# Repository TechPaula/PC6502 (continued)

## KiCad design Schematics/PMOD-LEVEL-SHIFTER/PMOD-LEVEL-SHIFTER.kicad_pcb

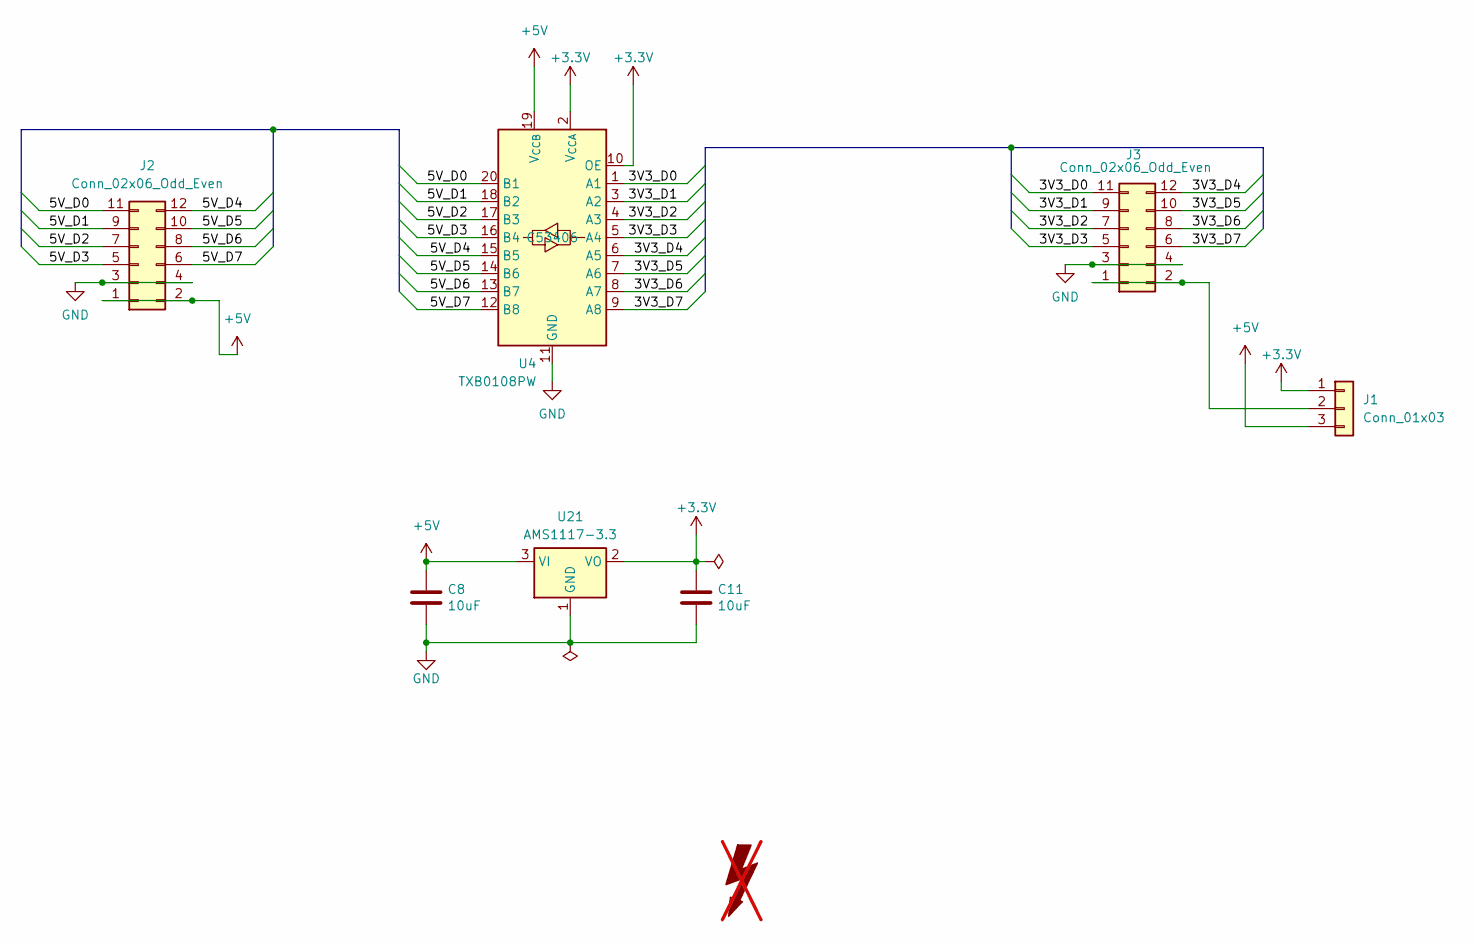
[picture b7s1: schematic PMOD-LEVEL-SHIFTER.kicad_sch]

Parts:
C8, C11: 10uF; C_0805_2012Metric; ManufacturerPN C3216X7R1E475M085AB; LCSC C15850
FOX1: SYM_Flash_Large; Fox_avatar_18mm; LCSC DNF; not fitted
J1: Conn_01x03; PinHeader_1x03_P2.54mm_Vertical
J2: Conn_02x06_Odd_Even; PinHeader_2x06_P2.54mm_Horizontal
J3: Conn_02x06_Odd_Even; PinSocket_2x06_P2.54mm_Horizontal
U4: TXB0108PW; TSSOP-20_4.4x6.5mm_P0.65mm; LCSC C53406
U21: AMS1117-3.3; SOT-223-3_TabPin2; LCSC C6186

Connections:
+3.3V: C11.1, J1.1, U4.2 (V_{CCA}), U4.10 (OE), U21.2 (VO)
+5V: C8.1, J1.3, J2.1, J2.2, U4.19 (V_{CCB}), U21.3 (VI)
/3V3_D0: J3.11, U4.1 (A1)
/3V3_D1: J3.9, U4.3 (A2)
/3V3_D2: J3.7, U4.4 (A3)
/3V3_D3: J3.5, U4.5 (A4)
/3V3_D4: J3.12, U4.6 (A5)
/3V3_D5: J3.10, U4.7 (A6)
/3V3_D6: J3.8, U4.8 (A7)
/3V3_D7: J3.6, U4.9 (A8)
/5V_D0: J2.11, U4.20 (B1)
/5V_D1: J2.9, U4.18 (B2)
/5V_D2: J2.7, U4.17 (B3)
/5V_D3: J2.5, U4.16 (B4)
/5V_D4: J2.12, U4.15 (B5)
/5V_D5: J2.10, U4.14 (B6)
/5V_D6: J2.8, U4.13 (B7)
/5V_D7: J2.6, U4.12 (B8)
GND: C8.2, C11.2, J2.3, J2.4, J3.3, J3.4, U4.11 (GND), U21.1 (GND)
unnamed: J1.2, J3.1, J3.2

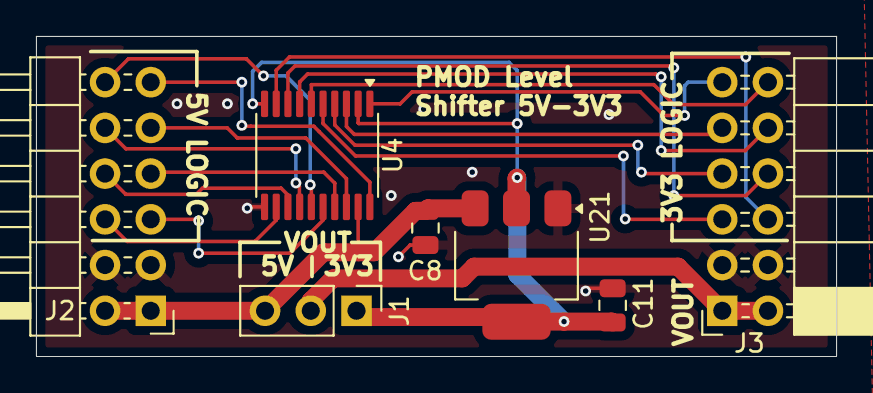
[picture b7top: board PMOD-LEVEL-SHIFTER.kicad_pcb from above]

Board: 4 copper layers, 44.5 x 17.8 mm, 8 parts (1 on the bottom side), 20 nets.

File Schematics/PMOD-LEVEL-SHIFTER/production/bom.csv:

Designator,Footprint,Quantity,Value,LCSC Part #
"C11, C8",0805,2,10uF,C15850
FOX1,Fox_avatar_18mm,1,SYM_Flash_Large,DNF
J1,PinHeader_1x03_P2.54mm_Vertical,1,Conn_01x03,
J2,PinHeader_2x06_P2.54mm_Horizontal,1,Conn_02x06_Odd_Even,
J3,PinSocket_2x06_P2.54mm_Horizontal,1,Conn_02x06_Odd_Even,
U21,SOT-223-3_TabPin2,1,AMS1117-3.3,C6186
U4,TSSOP-20_4.4x6.5mm_P0.65mm,1,TXB0108PW,C53406

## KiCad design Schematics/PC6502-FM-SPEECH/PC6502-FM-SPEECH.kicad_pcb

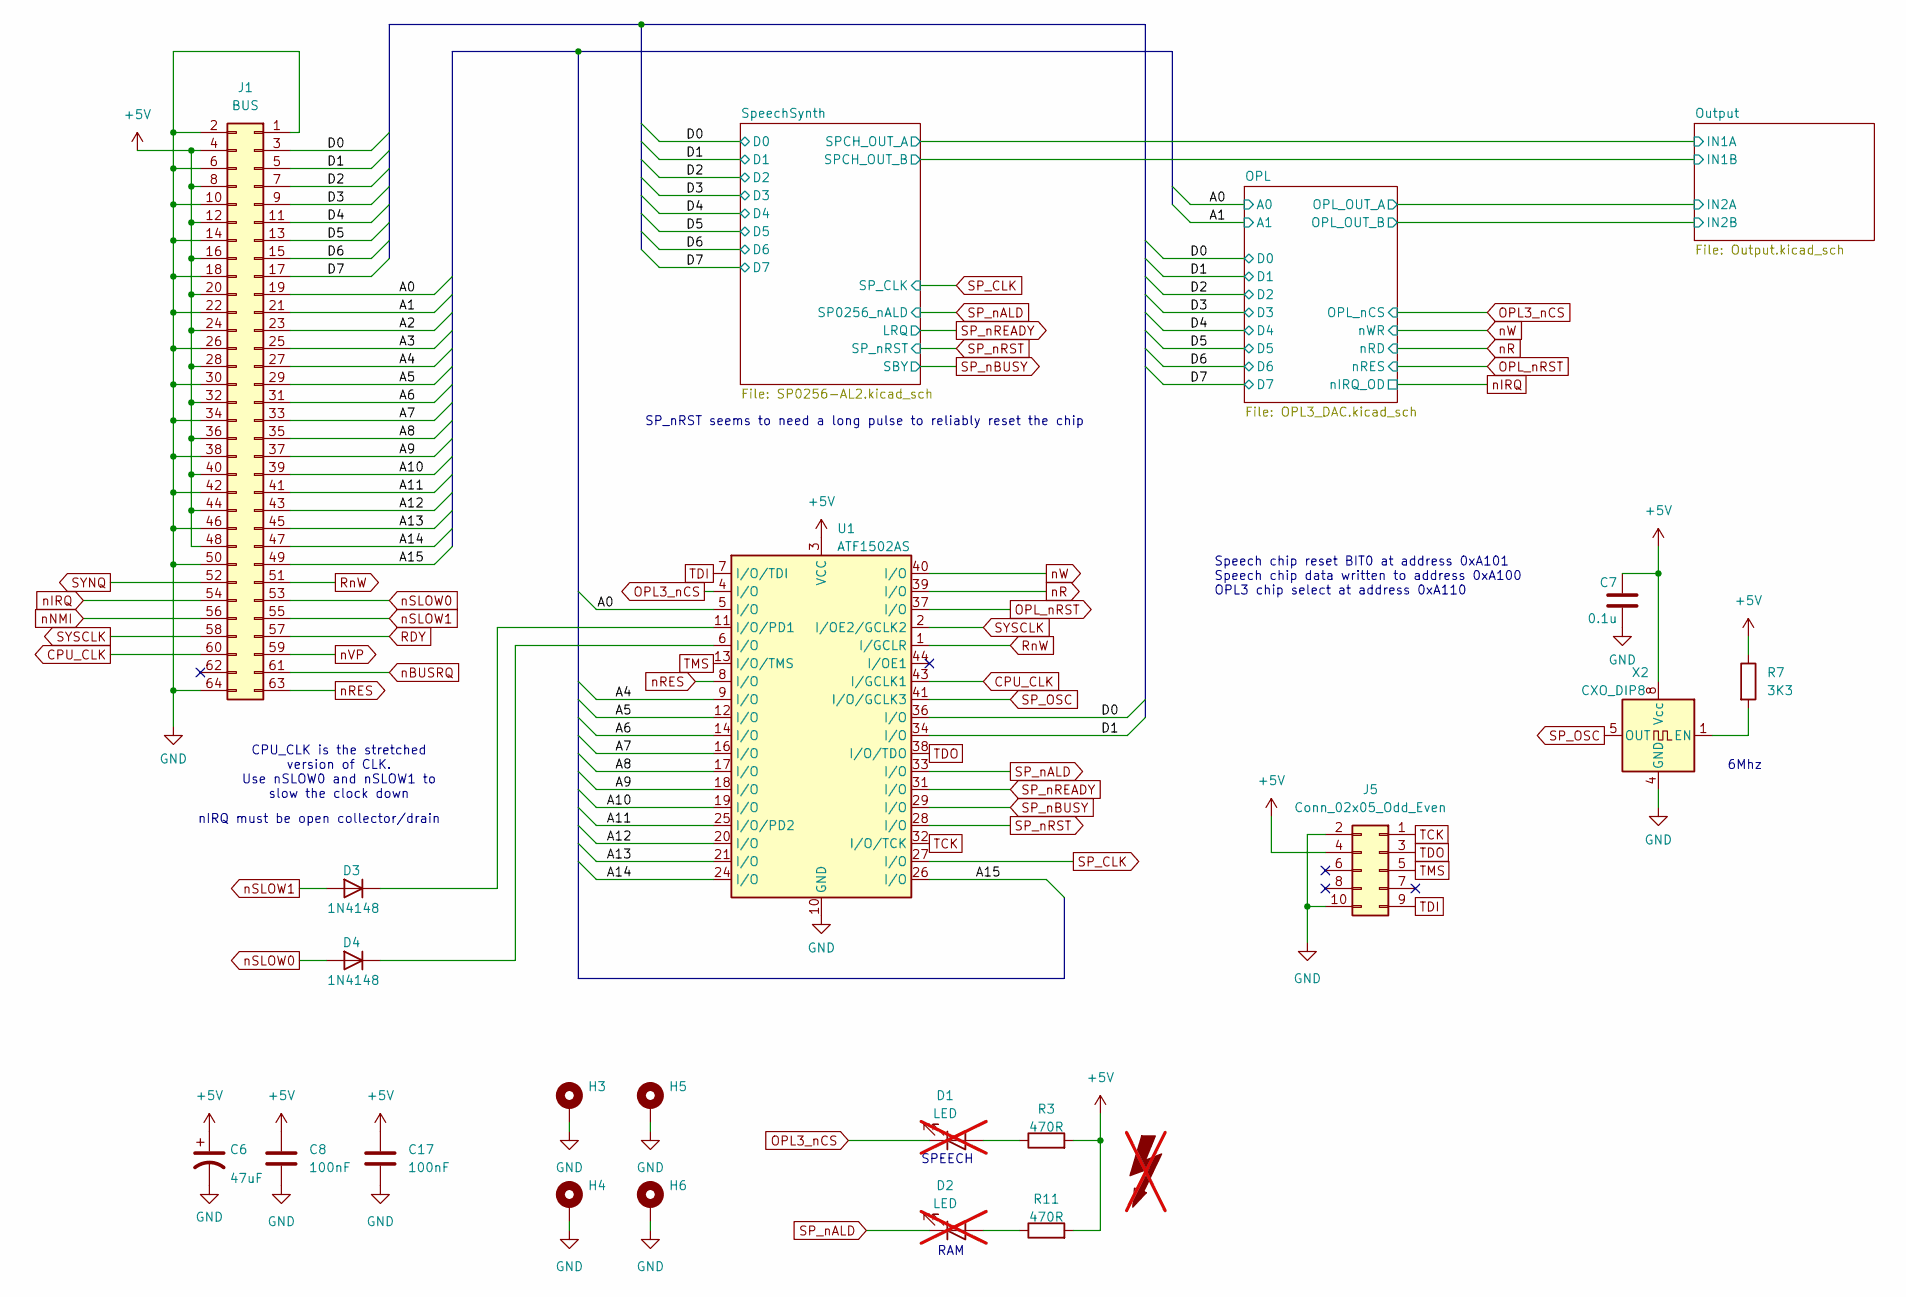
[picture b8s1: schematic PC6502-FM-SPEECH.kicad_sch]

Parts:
C6: 47uF; C_1206_3216Metric; LCSC C96123
C7: 0.1u; C_0603_1608Metric; ManufacturerPN C0603C104K3RAC7867
C8, C17: 100nF; C_0603_1608Metric
D1, D2: LED; LTL4221NHBP; LCSC DNF; not fitted
D3, D4: 1N4148; D_DO-35_SOD27_P7.62mm_Horizontal; LCSC DNF
FOX1: SYM_Flash_Large; Fox_avatar_18mm; LCSC DNF; not fitted
H3, H4, H5, H6: MountingHole_Pad; MountingHole_3.2mm_M3_Pad_TopBottom; LCSC DNF
J1: BUS; PinSocket_2x32_P2.54mm_Vertical; LCSC DNF
J5: Conn_02x05_Odd_Even; PinHeader_2x05_P2.54mm_Vertical; LCSC DNF
R3, R11: 470R; R_0603_1608Metric_Pad0.98x0.95mm_HandSolder; LCSC C23179
R7: 3K3; R_0603_1608Metric_Pad0.98x0.95mm_HandSolder; LCSC C25890
U1: ATF1502AS; PLCC-44_THT-Socket; LCSC DNF
X2: CXO_DIP8; Oscillator_DIP-8; LCSC DNF

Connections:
+5V: C6.1, C7.1, C8.1, C17.1, J1.4, J1.8, J1.12, J1.16, J1.20, J1.24, J1.28, J1.32, J1.36, J1.40, J1.44, J1.48, J5.4, R3.2, R7.1, R11.2, U1.3 (VCC), U1.15 (VCC), U1.23 (VCC), U1.35 (VCC), X2.8 (Vcc); also elsewhere on the board
/A0: J1.19, U1.5 (I/O); also elsewhere on the board
/A1: J1.21; also elsewhere on the board
/A2: J1.23
/A3: J1.25
/A4: J1.27, U1.9 (I/O)
/A5: J1.29, U1.12 (I/O)
/A6: J1.31, U1.14 (I/O)
/A7: J1.33, U1.16 (I/O)
/A8: J1.35, U1.17 (I/O)
/A9: J1.37, U1.18 (I/O)
/A10: J1.39, U1.19 (I/O)
/A11: J1.41, U1.25 (I/O/PD2)
/A12: J1.43, U1.20 (I/O)
/A13: J1.45, U1.21 (I/O)
/A14: J1.47, U1.24 (I/O)
/A15: J1.49, U1.26 (I/O)
/D0: J1.3, U1.36 (I/O); also elsewhere on the board
/D1: J1.5, U1.34 (I/O); also elsewhere on the board
/D2: J1.7; also elsewhere on the board
/D3: J1.9; also elsewhere on the board
/D4: J1.11; also elsewhere on the board
/D5: J1.13; also elsewhere on the board
/D6: J1.15; also elsewhere on the board
/D7: J1.17; also elsewhere on the board
CPU_CLK: J1.60, U1.43 (I/GCLK1)
GND: C6.2, C7.2, C8.2, C17.2, H3.1, H4.1, H5.1, H6.1, J1.1, J1.2, J1.6, J1.10, J1.14, J1.18, J1.22, J1.26, J1.30, J1.34, J1.38, J1.42, J1.46, J1.50, J1.64, J5.2, J5.10, U1.10 (GND), U1.22 (GND), U1.30 (GND), U1.42 (GND), X2.4 (GND); also elsewhere on the board
unnamed: D1.2 (A), R3.1
unnamed: D2.2 (A), R11.1
unnamed: D3.1 (K), U1.11 (I/O/PD1)
unnamed: D4.1 (K), U1.6 (I/O)
unnamed: R7.2, X2.1 (EN)
OPL3_nCS: D1.1 (K), U1.4 (I/O); also elsewhere on the board
OPL_nRST: U1.37 (I/O); also elsewhere on the board
RDY: J1.57
RnW: J1.51, U1.1 (I/GCLR)
SP_CLK: U1.27 (I/O); also elsewhere on the board
SP_OSC: U1.41 (I/O/GCLK3), X2.5 (OUT)
SP_nALD: D2.1 (K), U1.33 (I/O); also elsewhere on the board
SP_nBUSY: U1.29 (I/O); also elsewhere on the board
SP_nREADY: U1.31 (I/O); also elsewhere on the board
SP_nRST: U1.28 (I/O); also elsewhere on the board
SYNQ: J1.52
SYSCLK: J1.58, U1.2 (I/OE2/GCLK2)
TCK: J5.1, U1.32 (I/O/TCK)
TDI: J5.9, U1.7 (I/O/TDI)
TDO: J5.3, U1.38 (I/O/TDO)
TMS: J5.5, U1.13 (I/O/TMS)
nBUSRQ: J1.61
nIRQ: J1.54; also elsewhere on the board
nNMI: J1.56
nR: U1.39 (I/O); also elsewhere on the board
nRES: J1.63, U1.8 (I/O)
nSLOW0: D4.2 (A), J1.53
nSLOW1: D3.2 (A), J1.55
nVP: J1.59
nW: U1.40 (I/O); also elsewhere on the board

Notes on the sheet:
RAM
Speech chip reset BIT0 at address 0xA101 Speech chip data written to address 0xA100 OPL3 chip select at address 0xA110
SP_nRST seems to need a long pulse to reliably reset the chip
SPEECH
CPU_CLK is the stretched version of CLK. Use nSLOW0 and nSLOW1 to slow the clock down
6Mhz
nIRQ must be open collector/drain

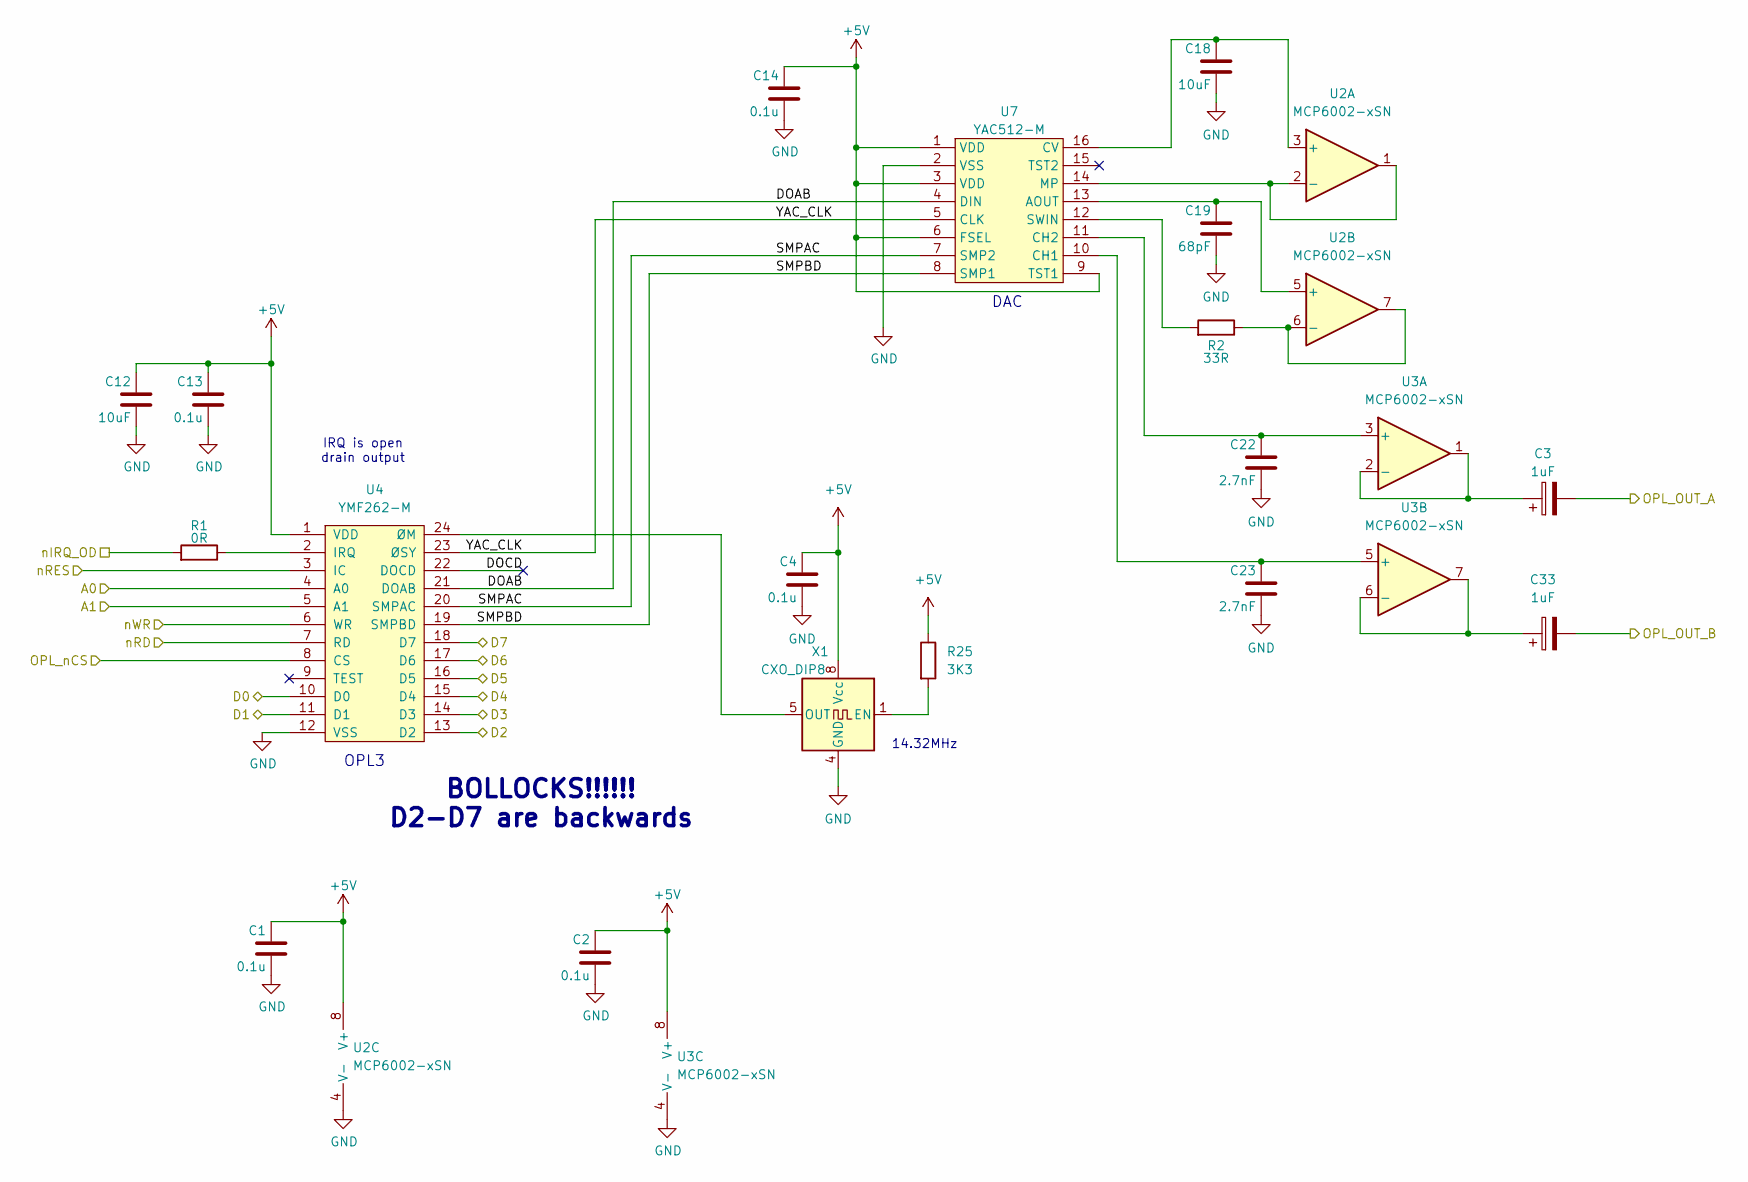
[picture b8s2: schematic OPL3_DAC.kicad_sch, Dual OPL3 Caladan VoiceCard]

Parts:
C1, C2, C4, C13, C14: 0.1u; C_0603_1608Metric; ManufacturerPN C0603C104K3RAC7867
C3, C33: 1uF; CP_EIA-3216-18_Kemet-A
C12: 10uF; C_1206_3216Metric; ManufacturerPN CL21X106KOQNNNE
C18: 10uF; C_0805_2012Metric
C19: 68pF; C_0603_1608Metric; ManufacturerPN CL21X106KOQNNNE
C22, C23: 2.7nF; C_0603_1608Metric; ManufacturerPN CL21X106KOQNNNE
R1: 0R; R_0603_1608Metric
R2: 33R; R_0603_1608Metric
R25: 3K3; R_0603_1608Metric_Pad0.98x0.95mm_HandSolder; LCSC C25890
U2, U3: MCP6002-xSN; SOIC-8_5.3x5.3mm_P1.27mm
U4: YMF262-M; SOIC-24W_7.5x15.4mm_P1.27mm
U7: YAC512-M; SOIC-16W_5.3x10.2mm_P1.27mm
X1: CXO_DIP8; Oscillator_DIP-8; LCSC DNF

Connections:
+5V: C1.1, C2.1, C4.1, C12.1, C13.1, C14.1, R25.1, U2.8 (V+), U3.8 (V+), U4.1 (VDD), U7.1 (VDD), U7.3 (VDD), U7.6 (FSEL), U7.9 (TST1), X1.8 (Vcc); also elsewhere on the board
/A0: U4.4 (A0); also elsewhere on the board
/A1: U4.5 (A1); also elsewhere on the board
/D0: U4.10 (D0); also elsewhere on the board
/D1: U4.11 (D1); also elsewhere on the board
/D2: U4.13 (D2); also elsewhere on the board
/D3: U4.14 (D3); also elsewhere on the board
/D4: U4.15 (D4); also elsewhere on the board
/D5: U4.16 (D5); also elsewhere on the board
/D6: U4.17 (D6); also elsewhere on the board
/D7: U4.18 (D7); also elsewhere on the board
/OPL/DOAB: U4.21 (DOAB), U7.4 (DIN)
/OPL/DOCD: U4.22 (DOCD)
/OPL/OPL_OUT_A: C3.2; also elsewhere on the board
/OPL/OPL_OUT_B: C33.2; also elsewhere on the board
/OPL/SMPAC: U4.20 (SMPAC), U7.7 (SMP2)
/OPL/SMPBD: U4.19 (SMPBD), U7.8 (SMP1)
/OPL/YAC_CLK: U4.23 (ØSY), U7.5 (CLK)
GND: C1.2, C2.2, C4.2, C12.2, C13.2, C14.2, C18.2, C19.2, C22.2, C23.2, U2.4 (V-), U3.4 (V-), U4.12 (VSS), U7.2 (VSS), X1.4 (GND); also elsewhere on the board
unnamed: C18.1, U2.3 (+), U7.16 (CV)
unnamed: U2.1, U2.2 (-), U7.14 (MP)
unnamed: C19.1, U2.5 (+), U7.13 (AOUT)
unnamed: R2.1, U2.6 (-), U2.7
unnamed: C22.1, U3.3 (+), U7.11 (CH2)
unnamed: C3.1, U3.1, U3.2 (-)
unnamed: C23.1, U3.5 (+), U7.10 (CH1)
unnamed: C33.1, U3.6 (-), U3.7
unnamed: R1.1, U4.2 (IRQ)
unnamed: U4.24 (ØM), X1.5 (OUT)
unnamed: R2.2, U7.12 (SWIN)
unnamed: R25.2, X1.1 (EN)
OPL3_nCS: U4.8 (CS); also elsewhere on the board
OPL_nRST: U4.3 (IC); also elsewhere on the board
nIRQ: R1.2; also elsewhere on the board
nR: U4.7 (RD); also elsewhere on the board
nW: U4.6 (WR); also elsewhere on the board

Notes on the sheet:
IRQ is open drain output
OPL3
DAC
BOLLOCKS!!!!!! D2-D7 are backwards
14.32MHz

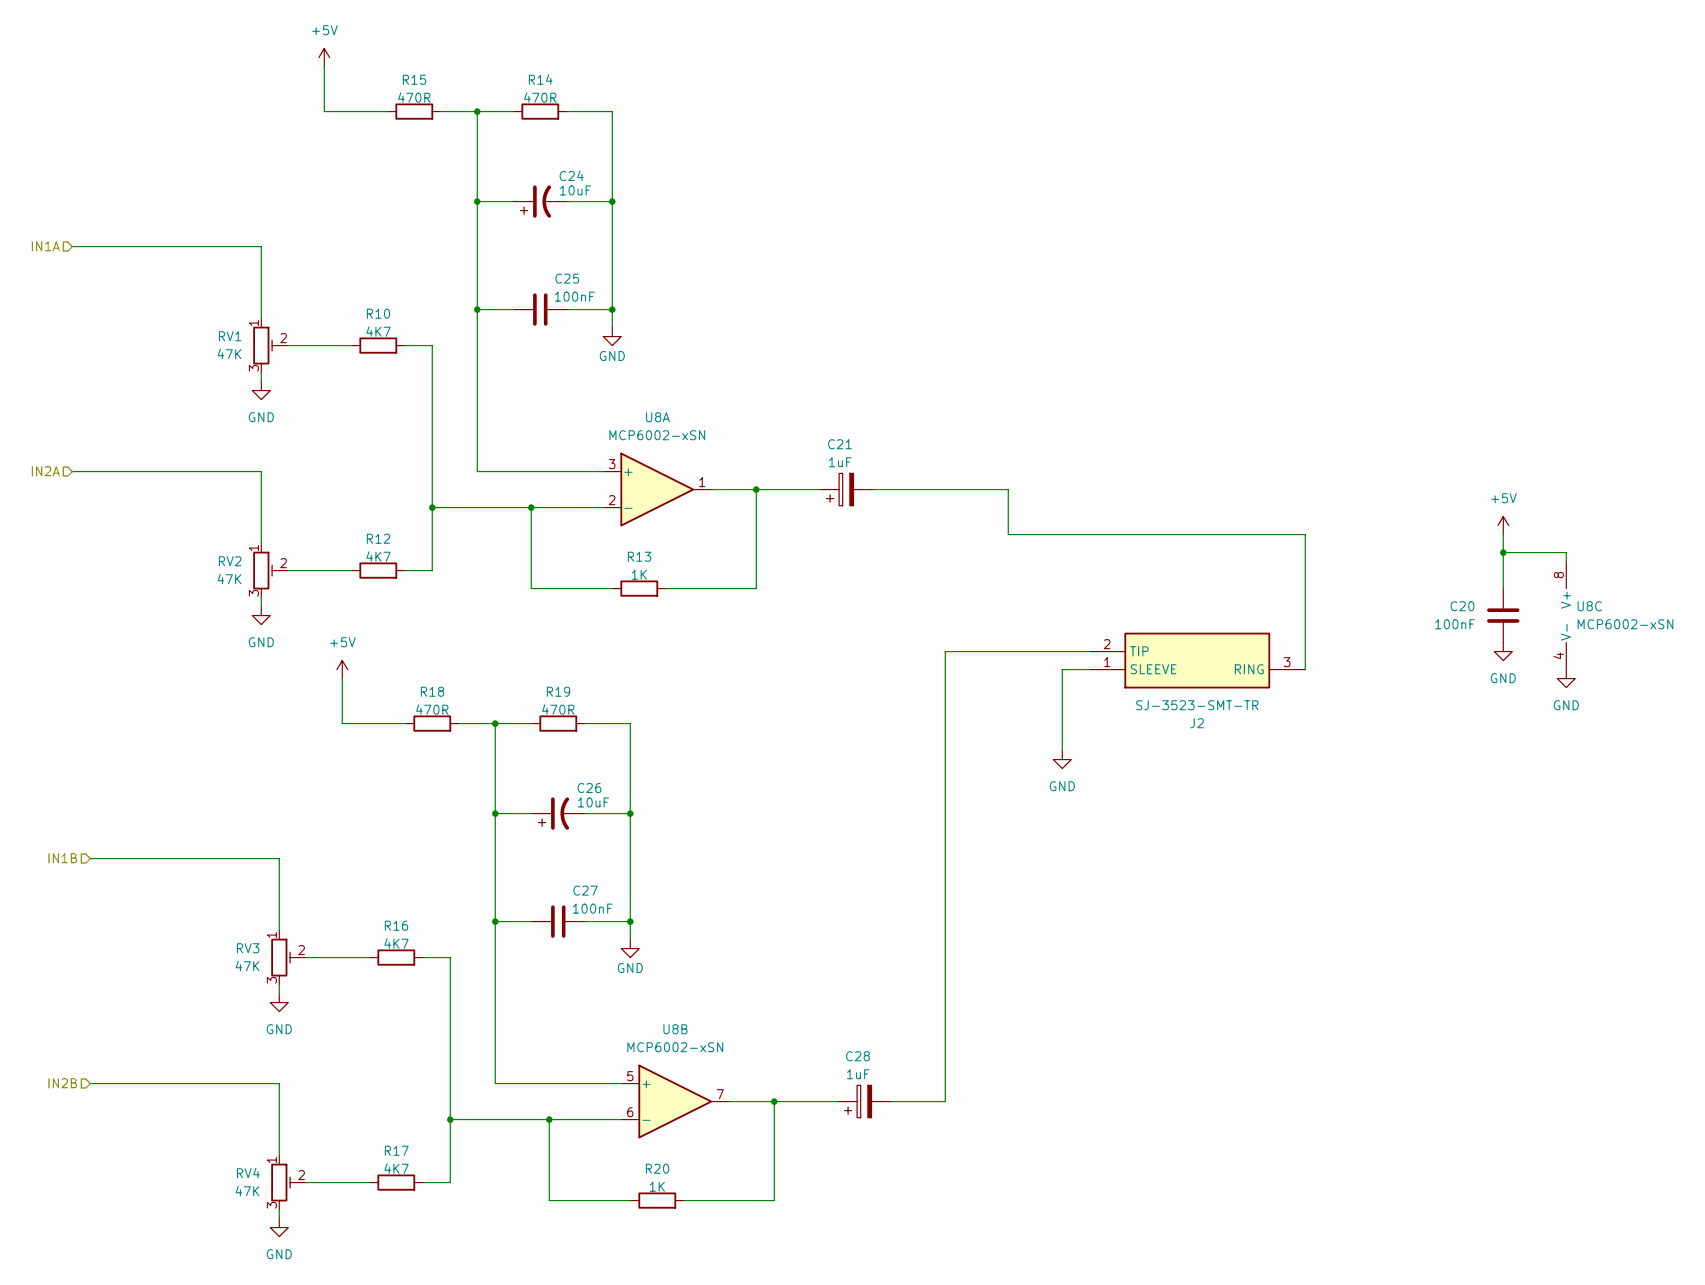
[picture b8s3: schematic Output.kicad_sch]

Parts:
C20, C25, C27: 100nF; C_0603_1608Metric
C21, C28: 1uF; CP_EIA-3216-18_Kemet-A
C24, C26: 10uF; C_0805_2012Metric; LCSC C96123
J2: SJ-3523-SMT-TR; SJ3523SMTTR; Mouser Part Number 490-SJ-3523-SMT-TR
R10, R12, R16, R17: 4K7; R_0603_1608Metric_Pad0.98x0.95mm_HandSolder; LCSC C23179
R13, R20: 1K; R_0603_1608Metric_Pad0.98x0.95mm_HandSolder; LCSC C23179
R14, R15, R18, R19: 470R; R_0603_1608Metric_Pad0.98x0.95mm_HandSolder; LCSC C23179
RV1, RV2, RV3, RV4: 47K; Potentiometer_Piher_PT-10-H01_Horizontal
U8: MCP6002-xSN; SOIC-8_5.3x5.3mm_P1.27mm

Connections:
+5V: C20.1, R15.1, R18.1, U8.8 (V+); also elsewhere on the board
/OPL/OPL_OUT_A: RV2.1; also elsewhere on the board
/OPL/OPL_OUT_B: RV4.1; also elsewhere on the board
/Output/IN1A: RV1.1; also elsewhere on the board
/Output/IN1B: RV3.1; also elsewhere on the board
GND: C20.2, C24.2, C25.1, C26.2, C27.1, J2.1 (SLEEVE), R14.2, R19.2, RV1.3, RV2.3, RV3.3, RV4.3, U8.4 (V-); also elsewhere on the board
unnamed: C21.1, R13.2, U8.1
unnamed: C28.1, R20.2, U8.7
unnamed: C21.2, J2.3 (RING)
unnamed: C28.2, J2.2 (TIP)
unnamed: R10.1, RV1.2
unnamed: R12.1, RV2.2
unnamed: R16.1, RV3.2
unnamed: R17.1, RV4.2
unnamed: C24.1, C25.2, R14.1, R15.2, U8.3 (+)
unnamed: R10.2, R12.2, R13.1, U8.2 (-)
unnamed: C26.1, C27.2, R18.2, R19.1, U8.5 (+)
unnamed: R16.2, R17.2, R20.1, U8.6 (-)

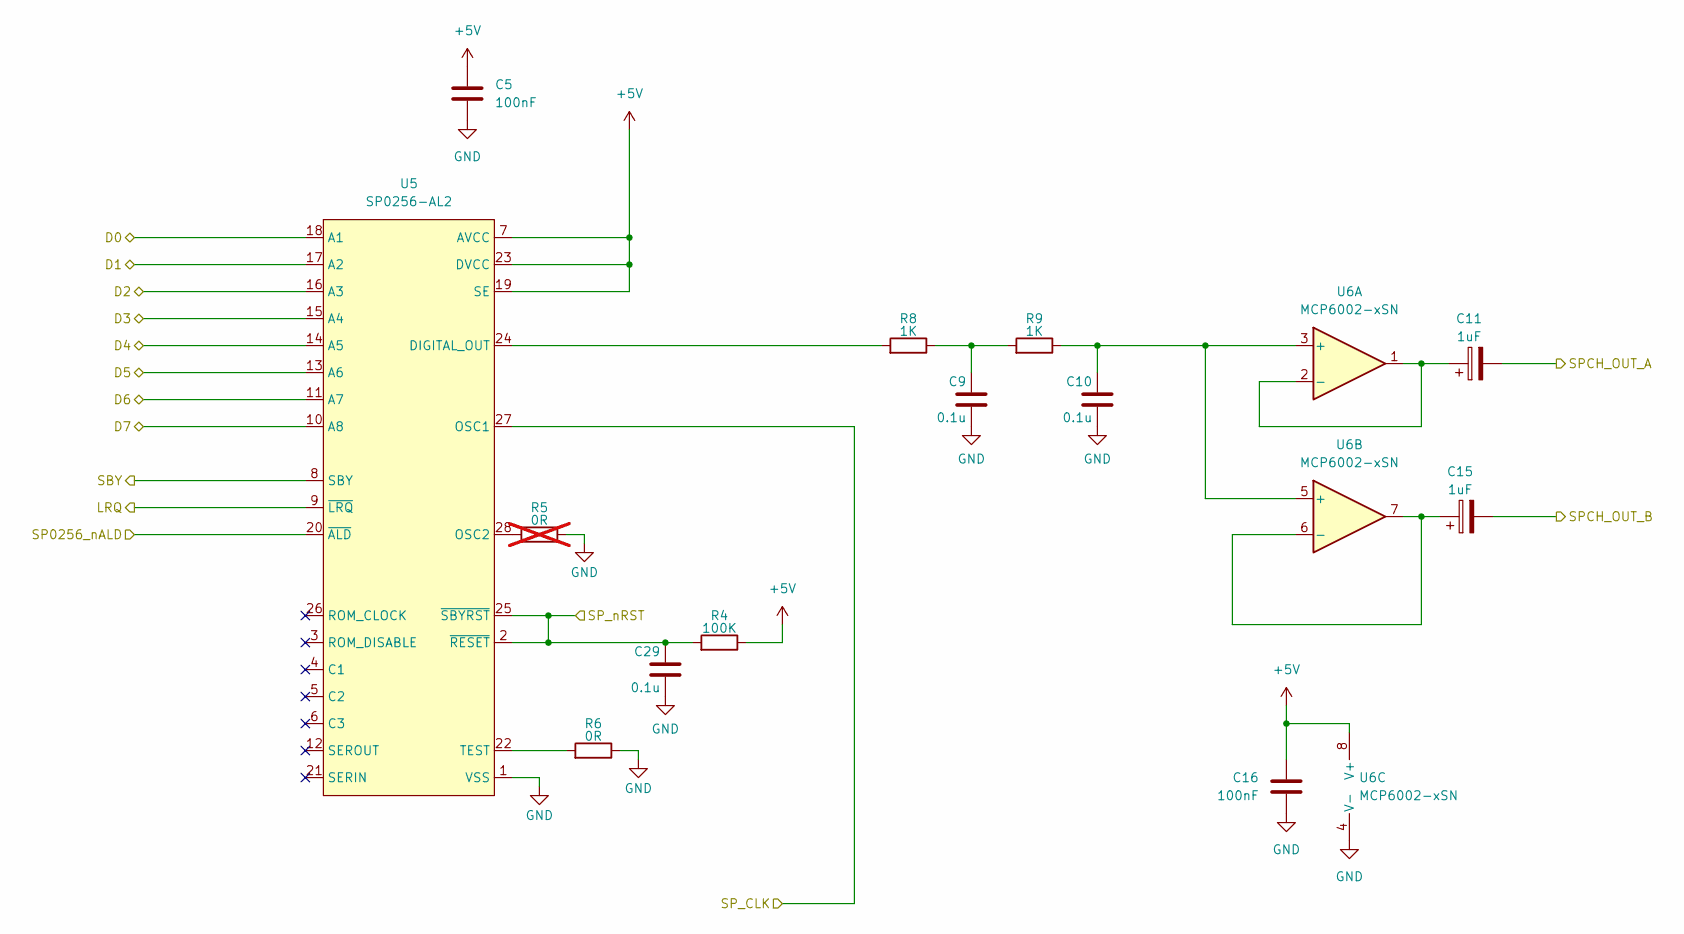
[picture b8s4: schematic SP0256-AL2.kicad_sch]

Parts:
C5, C16: 100nF; C_0603_1608Metric
C9, C10, C29: 0.1u; C_0603_1608Metric; ManufacturerPN C0603C104K3RAC7867
C11, C15: 1uF; CP_EIA-3216-18_Kemet-A
R4: 100K; R_0603_1608Metric
R5: 0R; R_0603_1608Metric; not fitted
R6: 0R; R_0603_1608Metric
R8, R9: 1K; R_0603_1608Metric
U5: SP0256-AL2; DIP-28_W15.24mm_Socket
U6: MCP6002-xSN; SOIC-8_5.3x5.3mm_P1.27mm

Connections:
+5V: C5.1, C16.1, R4.1, U5.7 (AVCC), U5.19 (SE), U5.23 (DVCC), U6.8 (V+); also elsewhere on the board
/D0: U5.18 (A1); also elsewhere on the board
/D1: U5.17 (A2); also elsewhere on the board
/D2: U5.16 (A3); also elsewhere on the board
/D3: U5.15 (A4); also elsewhere on the board
/D4: U5.14 (A5); also elsewhere on the board
/D5: U5.13 (A6); also elsewhere on the board
/D6: U5.11 (A7); also elsewhere on the board
/D7: U5.10 (A8); also elsewhere on the board
/Output/IN1A: C11.2; also elsewhere on the board
/Output/IN1B: C15.2; also elsewhere on the board
GND: C5.2, C9.2, C10.2, C16.2, C29.2, R5.1, R6.1, U5.1 (VSS), U6.4 (V-); also elsewhere on the board
unnamed: C9.1, R8.1, R9.2
unnamed: R8.2, U5.24 (DIGITAL_OUT)
unnamed: R5.2, U5.28 (OSC2)
unnamed: R6.2, U5.22 (TEST)
unnamed: C10.1, R9.1, U6.3 (+), U6.5 (+)
unnamed: C11.1, U6.1, U6.2 (-)
unnamed: C15.1, U6.6 (-), U6.7
SP_CLK: U5.27 (OSC1); also elsewhere on the board
SP_nALD: U5.20 (~ALD); also elsewhere on the board
SP_nBUSY: U5.8 (SBY); also elsewhere on the board
SP_nREADY: U5.9 (~LRQ); also elsewhere on the board
SP_nRST: C29.1, R4.2, U5.2 (~RESET), U5.25 (~SBYRST); also elsewhere on the board

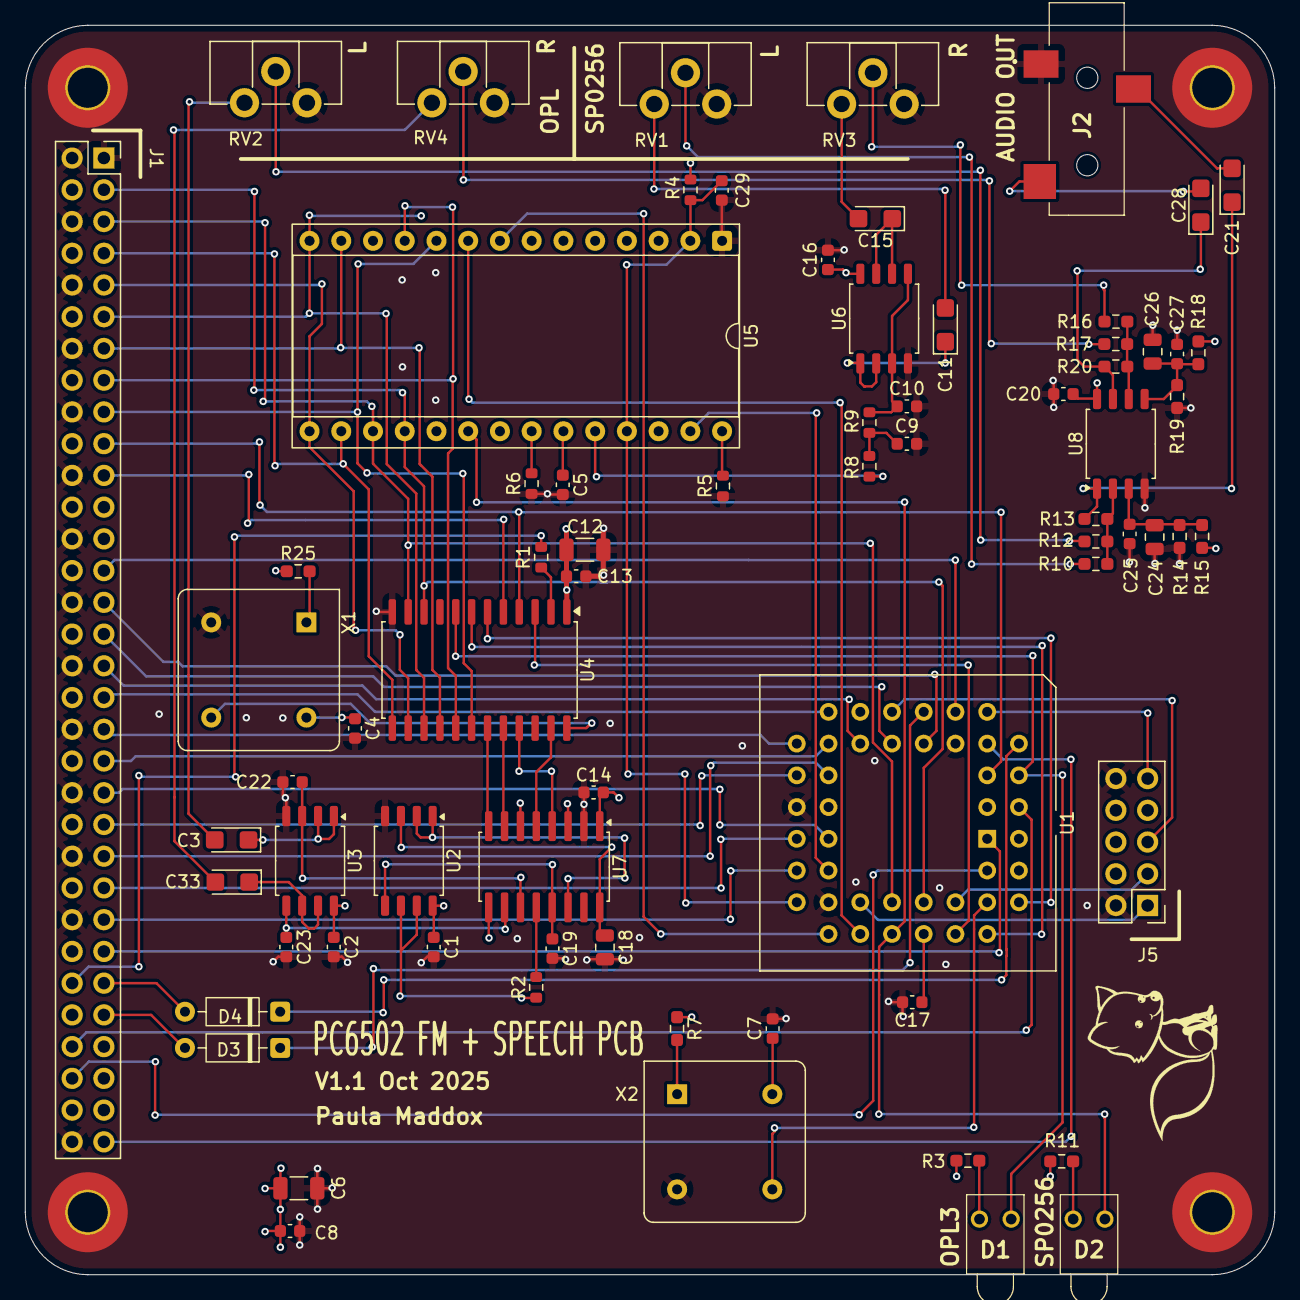
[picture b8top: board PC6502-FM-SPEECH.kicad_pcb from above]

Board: 4 copper layers, 100.0 x 100.0 mm, 77 parts (0 on the bottom side), 89 nets.

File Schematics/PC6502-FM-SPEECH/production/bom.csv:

Designator,Footprint,Quantity,Value,LCSC Part #
"C1, C10, C13, C14, C2, C4, C7, C9",0603,8,0.1u,
"C11, C15, C21, C28, C3, C33",CP_EIA-3216-18_Kemet-A,6,1uF,
C12,1206,1,10uF,
"C16, C17, C20, C25, C27, C5, C8",0603,7,100nF,
C18,0805,1,10uF,
C19,0603,1,68pF,
"C22, C23",0603,2,2.7nF,
"C24, C26",0805,2,10uF,C96123
C6,1206,1,47uF,C96123
"D1, D2",LTL4221NHBP,2,LED,DNF
"D3, D4",D_DO-35_SOD27_P7.62mm_Horizontal,2,1N4148,DNF
"H3, H4, H5, H6",MountingHole_3.2mm_M3_Pad_TopBottom,4,MountingHole_Pad,DNF
J1,PinSocket_2x32_P2.54mm_Vertical,1,BUS,DNF
J2,SJ3523SMTTR,1,SJ-3523-SMT-TR,
J5,PinHeader_2x05_P2.54mm_Vertical,1,Conn_02x05_Odd_Even,DNF
"R1, R4, R5, R6",0603,4,0R,
"R10, R12, R16, R17",0603,4,4K7,C23179
"R11, R14, R15, R18, R19, R3",0603,6,470R,C23179
"R13, R20",0603,2,1K,C23179
R2,0603,1,33R,
"R25, R7",0603,2,3K3,C25890
"R8, R9",0603,2,1K,
"RV1, RV2, RV3, RV4",Potentiometer_Piher_PT-10-H01_Horizontal,4,47K,
U1,PLCC-44_THT-Socket,1,ATF1502AS,DNF
"U2, U3, U6, U8",SOIC-8_5.3x5.3mm_P1.27mm,4,MCP6002-xSN,
U4,SOIC-24W_7.5x15.4mm_P1.27mm,1,YMF262-M,
U5,DIP-28_W15.24mm_Socket,1,SP0256-AL2,
U7,SOIC-16W_5.3x10.2mm_P1.27mm,1,YAC512-M,
"X1, X2",Oscillator_DIP-8,2,CXO_DIP8,DNF

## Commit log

2025-09-11 Initial Commit
    PCBs and CPLD code
2025-09-11 Updated Schematics
2025-09-11 Added .gitignore
2025-09-11 Updated Template and .gitignore
2025-09-11 Added firmware
    Added my modified version of Grant Searl's 6502 code.
    It builds with the correct addresses but is not yet tested.
2025-09-11 Update README.md
    Updated RAM usage table
2025-09-11 Updated RAM memory map
2025-09-13 Add Power/Storage PCB
    Also tidied template
2025-09-14 Further routing
    So far all DDR tracks are 22.4mm in length, or within 0.5mm (~2.5pS)
2025-09-20 Created V1.1 Schematic and PCB
    A LOT of changes from v1.00;
    removed clock stretcher (will now live in the CPLD)
    moved the USB interface direct to the PCB
    changed power pins
    Added extra capacitance
    Used Grant Searle's OSI basic and memory map to bring up the board
2025-09-20 Updated README
    added some detail of what is working and what is not, along with some pictures
2025-09-20 FT245 WRITE signal correction
    I had it marked as active low when it's active high, updated.
2025-09-20 FT245 label change
2025-09-21 V1.1 CPU, VIA and POWER PCBs uploaded
    A simpler CPU board (direct link to FT245R, 74161 removed and some tidying of tracks). Fixed a couple of floating inputs to RAM/ROM
    VIA is much simpler, having just the one VIA chip.
    POWER board has USB-PD and a 24VDC input for higher power stuff in the future.
2025-09-27 Tidy up and simplify
    Created schematic for FM & Speech sound board
    Made Storage board just for Compact Flash (CF) storage
    Routed Storage PCB
2025-10-02 Updated following testing
    New CPLD code for CPU and VIA
    Fixed mistakes with CPU Board and upped to Rev 1.2 (My Rev 1.1 has mods on)
    Updated README
2025-10-12 Ordered Storage, FM/Speech, Dual SPI and APPLE II slot PCBs
2025-10-14 CPU CPLD UPDATE!!
    CPU will now run at 14MHz with the updated code in the CPLD
    Begun assembly of Speech/FM board
2025-10-16 SP0256 Speech synth working
    SP0256 now working, couple of extra wires needed, but PCB and schematics updated.
    Test code (SP0256_TEST3.BAS) created.
    CPLD updated.
2025-10-16 remove incorrect JED file
2025-10-19 Added more images / dual SPI CPLD code
    Added more photos,
    Added dual SPI CPLD code
    Added basic test code for dual SPI
2025-10-19 Compact Flash CPLD and test code
    This is the CPLD files and BASIC test files for the compact flash card.
2025-10-19 Firmware file corrected.
2025-10-23 Updated Schematics and CPLD files
    Files updated for the CPU & FM Speech board
    Also revised CPLDs for CPU, VIA and Compact Flasg
2025-10-23 Updated silk screen
    Updated silk screen on CPU board to V1.3
2025-10-24 Added comments to .BAS files
2025-10-24 Fixed output on FM/Speech card
    The ring and sleeve were the wrong way around.
2025-11-02 KEYBoard/TFT interface schematics
    Rev 1.00 boards ordered.
2025-11-02 Keyboard files created and ordered.
2025-11-02 Created PMOD level shifter
    Made a simple 5V - 3,3V level shifter so I can test a display.
2025-11-02 More BASIC programs
    Working on a load/save and just trying to figure out how basic is stored in RAM.
    Also working on a Transputer TRAM test code
2025-11-02 Added AIISLOT CPLD files
2025-11-07 More BASIC programs
    extra mandlebrot test, new OPL3 test and twinkle tinkle little star test.
2025-11-12 Keyboard code and schematics
    Updated the Schematics and have a mostly functioning keyboard (can't turn off caps lock yet)
2025-11-12 Starting to tinker with OSI basic to add in extra features
    waiting on ROM emulator to arrive to test and do further work.
2025-11-12 Add image of keybed
2025-11-12 Update README.md
    Fix typo
2025-11-12 Update README.md
    Updated memory map
2025-11-15 Updated CPU to Rev 1.4
    VErsion 1.4 of CPU board connects A15 direct to RAM and should allow me to get more than 32K of RAM available.
2025-11-15 KeyTFT to Rev 1.1
    COmplete revamp of Schamtic and PCB, to make things simpler, and hopefully a bit quicker.
2025-11-15 Begun work on Firmware
    Added placeholders for LOAD, SAVE and DIR
    Added script to build files
    Modified osi_bas.s to make it build with newer versions of ca65/ld65
2025-11-15 rework broken BASIC source file
2025-11-16 KeyBed code
    Tidyup and trying to figure out a bug
2025-11-18 Added EhBASIC to repository
    There is now EhBASIC and EhBASIC with Wozmon ported to the PC6502.
    Thank you to SHONKY for sorting this :)
2025-11-19 Work on display test code
2025-11-20 Working on SPI display test
2025-11-20 fixed bug in VIA decode logic
2025-11-20 VIA CPLD
    fix typo, build and program
2025-11-21 Added keybed image
    fully assembled keybed image.
2025-11-23 Working on spi display configuration
    sadly not working
2025-11-23 display debugging
    added output from teensy console
2025-11-29 CPLD Updates
    This Updates the CPU CPLD to work with V1.4 of the CPU board and gives BOTH nSLOW pins control of CPU clock stretching
    Also added the CPLD code for the KEYTFT PCB
2025-11-29 Updated project file with correct names,
2025-12-06 updating KEYTFT CPLD
2025-12-06 FIXED CPLD FOR TFT
2025-12-06 Finally got display text working!
2025-12-06 Added code for showing mandlebrot on display
2025-12-14 Added basic tests for display, added transputer link adapter
2025-12-20 fixed 6551 chip select decode
2025-12-20 Added slow to keyboard CS
2025-12-20 working on keyboard debugging
2025-12-24 Updated Transputer CPLD and Basic code
    writing and reading to/from the TRAM now works!
2025-12-24 TRAM test tidy
    removed excess delays
2025-12-24 Uploaded pictures of modwire
2025-12-24 Added Dual transputer host card
2025-12-24 updated git ignore
2025-12-24 added image of transputer PCB
2025-12-28 Found an issue with Sound/Speech PCB, resolved
2025-12-28 Update KeyTFT CPLD
2025-12-29 updated keytft CPLD
    found a bug (or three) that was forcing the CPU slow. Display now runs at full clock speed, rather than having to slow it to 1/4 clock speed.
2025-12-29 Work on Display CPLD
    Working fine with 8MHz CPU_CLK.
    Doesn't work faster than that.
2025-12-29 Tidy CPLD comments
2025-12-29 Updated KeyTFT Schematic to include mods
2025-12-29 updated transputer test programs
2025-12-30 Fixed bug in transputer type test program
    fixed bug in CFTest program
2026-03-21 Changes I forgot to commit
